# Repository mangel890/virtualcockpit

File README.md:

# virtualcockpit
Virtual Boeing 737 Cockpit

This is a project to build my own Boeing 737 cockpit
It is based on Arduino and Flight Simulator

This is on early stages now, many more changes are needed

Arduino/ contains a arduino .ino file for the MCP of the 737

CNC/ Sketch developed for my CNC that helps drilling the panels

PCB/ Different boards developed for extending input and output in Arduino Mega

Drawings/ Sketch developed for printing the MCP of the 737

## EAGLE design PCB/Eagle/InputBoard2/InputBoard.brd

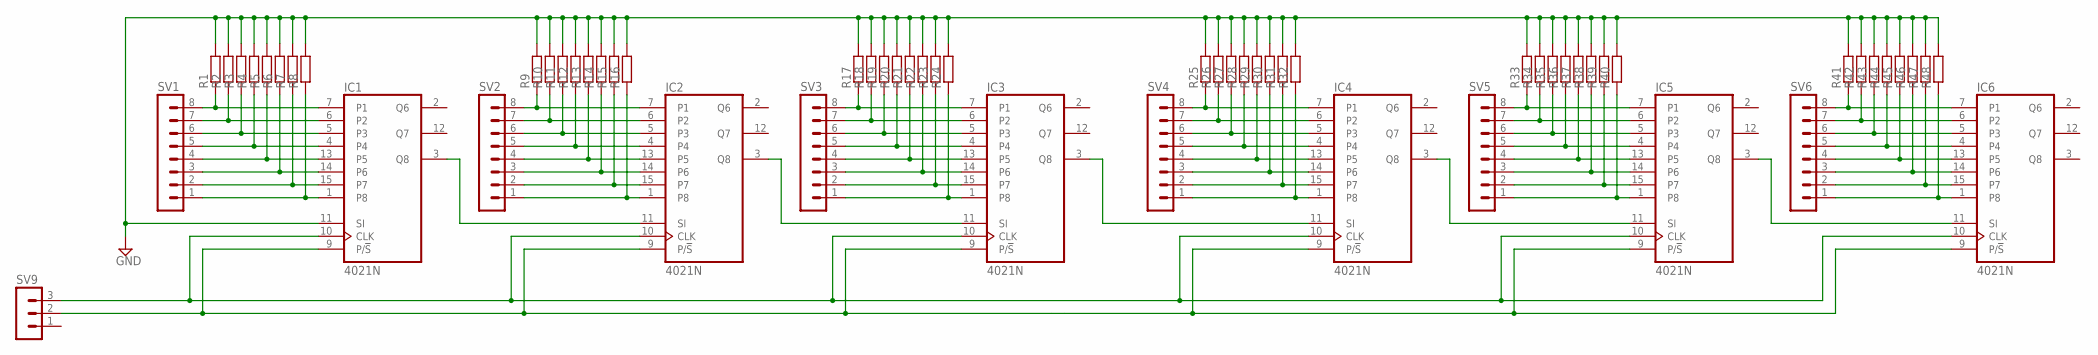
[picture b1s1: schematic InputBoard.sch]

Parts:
IC1, IC2, IC3, IC4, IC5, IC6: 4021N; DIL16
R1, R2, R3, R4, R5, R6, R7, R8, R9, R10, R11, R12, R13, R14, R15, R16, R17, R18, R19, R20, R21, R22, R23, R24, R25, R26, R27, R28, R29, R30, R31, R32, R33, R34, R35, R36, R37, R38, R39, R40, R41, R42, R43, R44, R45, R46, R47, R48: R-EU_0207/10; 0207/10
SV1, SV2, SV3, SV4, SV5, SV6: MA08-1
SV9: MA03-1

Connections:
GND: IC1.11 (SI), IC3.3 (Q8), IC4.11 (SI), R1.2, R2.2, R3.2, R4.2, R5.2, R6.2, R7.2, R8.2, R9.2, R10.2, R11.2, R12.2, R13.2, R14.2, R15.2, R16.2, R17.2, R18.2, R19.2, R20.2, R21.2, R22.2, R23.2, R24.2, R25.2, R26.2, R27.2, R28.2, R29.2, R30.2, R31.2, R32.2, R33.2, R34.2, R35.2, R36.2, R37.2, R38.2, R39.2, R40.2, R41.2, R42.2, R43.2, R44.2, R45.2, R46.2, R47.2, R48.2
unnamed: IC4.7 (P1), R25.1, SV4.8
unnamed: IC1.10 (CLK), IC2.10 (CLK), IC3.10 (CLK), IC4.10 (CLK), IC5.10 (CLK), IC6.10 (CLK), SV9.3
unnamed: IC1.3 (Q8), IC2.11 (SI)
unnamed: IC2.7 (P1), R9.1, SV2.8
unnamed: IC4.5 (P3), R27.1, SV4.6
unnamed: IC2.5 (P3), R11.1, SV2.6
unnamed: IC2.4, R12.1, SV2.5
unnamed: IC2.13 (P5), R13.1, SV2.4
unnamed: IC2.14 (P6), R14.1, SV2.3
unnamed: IC1.7 (P1), R1.1, SV1.8
unnamed: IC1.6 (P2), R2.1, SV1.7
unnamed: IC1.5 (P3), R3.1, SV1.6
unnamed: IC1.4, R4.1, SV1.5
unnamed: IC1.13 (P5), R5.1, SV1.4
unnamed: IC1.14 (P6), R6.1, SV1.3
unnamed: IC1.15 (P7), R7.1, SV1.2
unnamed: IC1.1 (P8), R8.1, SV1.1
unnamed: IC2.15 (P7), R15.1, SV2.2
unnamed: IC2.6 (P2), R10.1, SV2.7
unnamed: IC2.1 (P8), R16.1, SV2.1
unnamed: IC3.7 (P1), R17.1, SV3.8
unnamed: IC3.5 (P3), R19.1, SV3.6
unnamed: IC1.9 (P/!S), IC2.9 (P/!S), IC3.9 (P/!S), IC4.9 (P/!S), IC5.9 (P/!S), IC6.9 (P/!S), SV9.2
unnamed: IC3.4, R20.1, SV3.5
unnamed: IC3.13 (P5), R21.1, SV3.4
unnamed: IC3.14 (P6), R22.1, SV3.3
unnamed: IC3.15 (P7), R23.1, SV3.2
unnamed: IC3.6 (P2), R18.1, SV3.7
unnamed: IC3.1 (P8), R24.1, SV3.1
unnamed: IC4.4, R28.1, SV4.5
unnamed: IC2.3 (Q8), IC3.11 (SI)
unnamed: IC4.13 (P5), R29.1, SV4.4
unnamed: IC4.14 (P6), R30.1, SV4.3
unnamed: IC4.15 (P7), R31.1, SV4.2
unnamed: IC4.6 (P2), R26.1, SV4.7
unnamed: IC4.1 (P8), R32.1, SV4.1
unnamed: IC5.7 (P1), R33.1, SV5.8
unnamed: IC5.5 (P3), R35.1, SV5.6
unnamed: IC5.4, R36.1, SV5.5
unnamed: IC5.13 (P5), R37.1, SV5.4
unnamed: IC5.14 (P6), R38.1, SV5.3
unnamed: IC5.15 (P7), R39.1, SV5.2
unnamed: IC5.6 (P2), R34.1, SV5.7
unnamed: IC5.1 (P8), R40.1, SV5.1
unnamed: IC4.3 (Q8), IC5.11 (SI)
unnamed: IC6.7 (P1), R41.1, SV6.8
unnamed: IC6.5 (P3), R43.1, SV6.6
unnamed: IC6.4, R44.1, SV6.5
unnamed: IC6.13 (P5), R45.1, SV6.4
unnamed: IC6.14 (P6), R46.1, SV6.3
unnamed: IC6.15 (P7), R47.1, SV6.2
unnamed: IC6.6 (P2), R42.1, SV6.7
unnamed: IC6.1 (P8), R48.1, SV6.1
unnamed: IC5.3 (Q8), IC6.11 (SI)
VDD: IC1.16 (VDD), IC2.16 (VDD), IC3.16 (VDD), IC4.16 (VDD), IC5.16 (VDD), IC6.16 (VDD)
VSS: IC1.8 (VSS), IC2.8 (VSS), IC3.8 (VSS), IC4.8 (VSS), IC5.8 (VSS), IC6.8 (VSS)

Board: 2 copper layers, 61 parts (0 on the bottom side), 57 nets, no tracks yet.

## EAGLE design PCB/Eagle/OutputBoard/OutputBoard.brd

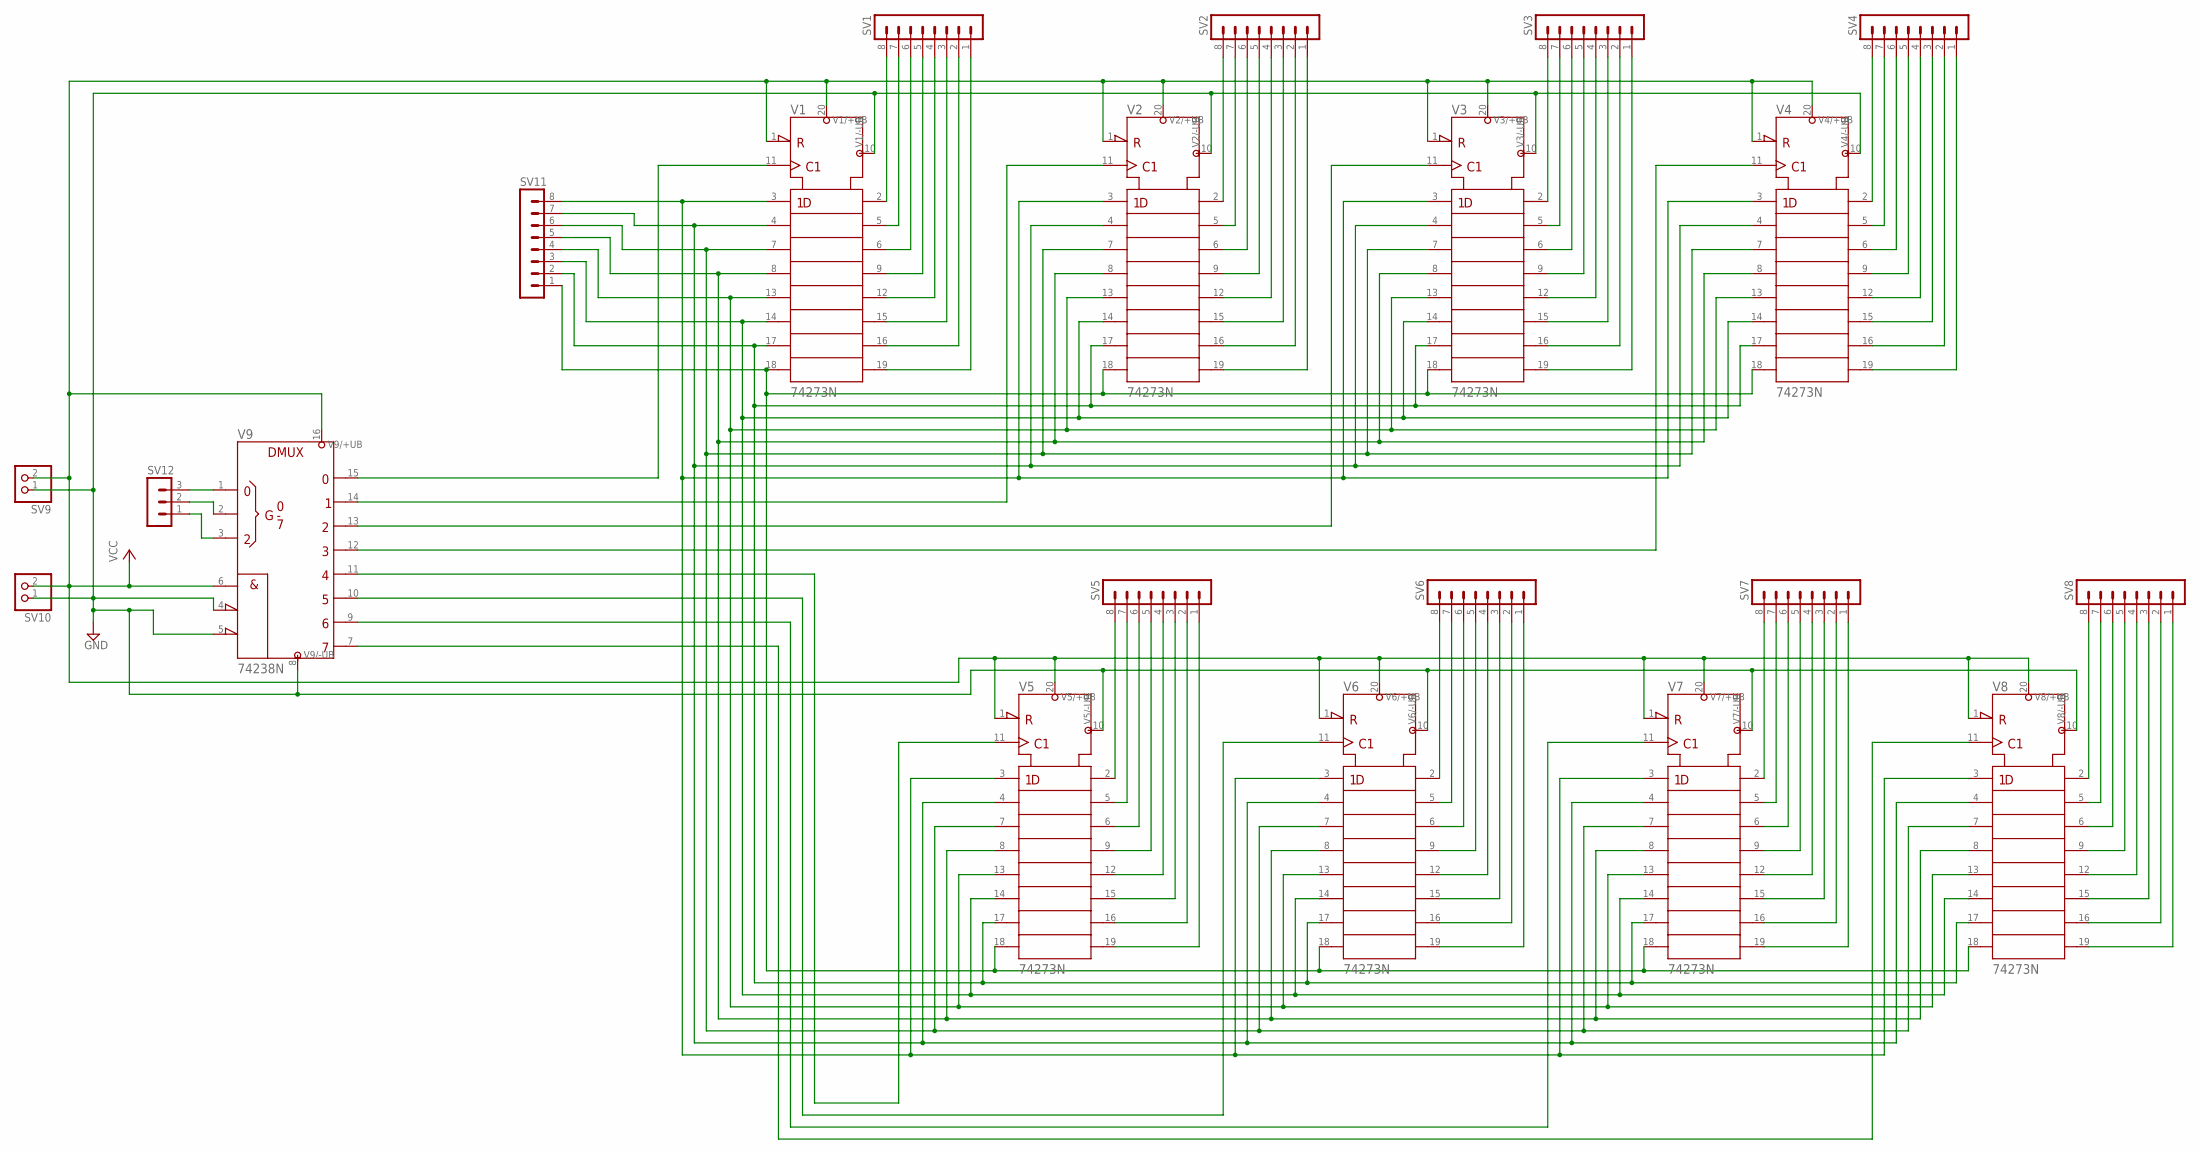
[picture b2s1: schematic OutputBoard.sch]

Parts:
SV1, SV2, SV3, SV4, SV5, SV6, SV7, SV8, SV11: MA08-1
SV9, SV10: PINHD-1X2; 1X02
SV12: MA03-1
V1, V2, V3, V4, V5, V6, V7, V8: 74273N; DIL20
V9: 74238N; DIL16

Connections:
BUS1: SV11.8, V1.3 (1D), V2.3 (1D), V3.3 (1D), V4.3 (1D), V5.3 (1D), V6.3 (1D), V7.3 (1D), V8.3 (1D)
DATA1: SV11.1, V1.18 (8D), V2.18 (8D), V3.18 (8D), V4.18 (8D), V5.18 (8D), V6.18 (8D), V7.18 (8D), V8.18 (8D)
DATA2: SV11.2, V1.17 (7D), V2.17 (7D), V3.17 (7D), V4.17 (7D), V5.17 (7D), V6.17 (7D), V7.17 (7D), V8.17 (7D)
DATA3: SV11.3, V1.14 (6D), V2.14 (6D), V3.14 (6D), V4.14 (6D), V5.14 (6D), V6.14 (6D), V7.14 (6D), V8.14 (6D)
DATA8: SV11.4, V1.13 (5D), V2.13 (5D), V3.13 (5D), V4.13 (5D), V5.13 (5D), V6.13 (5D), V7.13 (5D), V8.13 (5D)
GND: SV9.1, SV10.1, V1.10 (-UB), V2.10 (-UB), V3.10 (-UB), V4.10 (-UB), V5.10 (-UB), V6.10 (-UB), V7.10 (-UB), V8.10 (-UB), V9.4 (!G2A), V9.5 (!G2B), V9.8 (-UB)
unnamed: V3.11 (CLK), V9.13 (Y2)
unnamed: SV2.8, V2.2 (1Q)
unnamed: V1.11 (CLK), V9.15 (Y0)
unnamed: V2.11 (CLK), V9.14 (Y1)
unnamed: SV2.7, V2.5 (2Q)
unnamed: SV2.6, V2.6 (3Q)
unnamed: SV2.5, V2.9 (4Q)
unnamed: SV2.4, V2.12 (5Q)
unnamed: SV2.3, V2.15 (6Q)
unnamed: SV2.2, V2.16 (7Q)
unnamed: SV2.1, V2.19 (8Q)
unnamed: SV1.8, V1.2 (1Q)
unnamed: SV12.2, V9.2 (B)
unnamed: SV12.1, V9.3 (C)
unnamed: SV5.8, V5.2 (1Q)
unnamed: SV1.7, V1.5 (2Q)
unnamed: SV1.6, V1.6 (3Q)
unnamed: SV1.5, V1.9 (4Q)
unnamed: SV1.4, V1.12 (5Q)
unnamed: SV12.3, V9.1 (A)
unnamed: SV5.7, V5.5 (2Q)
unnamed: SV5.6, V5.6 (3Q)
unnamed: SV1.3, V1.15 (6Q)
unnamed: SV1.2, V1.16 (7Q)
unnamed: SV1.1, V1.19 (8Q)
unnamed: V4.11 (CLK), V9.12 (Y3)
unnamed: V5.11 (CLK), V9.11 (Y4)
unnamed: V6.11 (CLK), V9.10 (Y5)
unnamed: SV11.7, V1.4 (2D), V2.4 (2D), V3.4 (2D), V4.4 (2D), V5.4 (2D), V6.4 (2D), V7.4 (2D), V8.4 (2D)
unnamed: SV3.8, V3.2 (1Q)
unnamed: SV3.7, V3.5 (2Q)
unnamed: SV3.6, V3.6 (3Q)
unnamed: SV3.5, V3.9 (4Q)
unnamed: SV3.4, V3.12 (5Q)
unnamed: SV3.3, V3.15 (6Q)
unnamed: SV3.2, V3.16 (7Q)
unnamed: SV3.1, V3.19 (8Q)
unnamed: SV4.8, V4.2 (1Q)
unnamed: SV4.7, V4.5 (2Q)
unnamed: SV4.6, V4.6 (3Q)
unnamed: SV4.5, V4.9 (4Q)
unnamed: SV4.4, V4.12 (5Q)
unnamed: SV4.3, V4.15 (6Q)
unnamed: SV4.2, V4.16 (7Q)
unnamed: SV4.1, V4.19 (8Q)
unnamed: SV11.6, V1.7 (3D), V2.7 (3D), V3.7 (3D), V4.7 (3D), V5.7 (3D), V6.7 (3D), V7.7 (3D), V8.7 (3D)
unnamed: SV11.5, V1.8 (4D), V2.8 (4D), V3.8 (4D), V4.8 (4D), V5.8 (4D), V6.8 (4D), V7.8 (4D), V8.8 (4D)
unnamed: SV6.8, V6.2 (1Q)
unnamed: SV6.7, V6.5 (2Q)
unnamed: SV6.6, V6.6 (3Q)
unnamed: SV6.5, V6.9 (4Q)
unnamed: SV6.4, V6.12 (5Q)
unnamed: SV6.3, V6.15 (6Q)
unnamed: SV6.2, V6.16 (7Q)
unnamed: SV6.1, V6.19 (8Q)
unnamed: SV7.8, V7.2 (1Q)
unnamed: SV7.7, V7.5 (2Q)
unnamed: SV7.6, V7.6 (3Q)
unnamed: SV7.5, V7.9 (4Q)
unnamed: SV7.4, V7.12 (5Q)
unnamed: SV7.3, V7.15 (6Q)
unnamed: SV7.2, V7.16 (7Q)
unnamed: SV7.1, V7.19 (8Q)
unnamed: V7.11 (CLK), V9.9 (Y6)
unnamed: SV8.8, V8.2 (1Q)
unnamed: SV8.7, V8.5 (2Q)
unnamed: SV8.6, V8.6 (3Q)
unnamed: SV8.5, V8.9 (4Q)
unnamed: SV8.4, V8.12 (5Q)
unnamed: SV8.3, V8.15 (6Q)
unnamed: SV8.2, V8.16 (7Q)
unnamed: SV8.1, V8.19 (8Q)
unnamed: SV5.5, V5.9 (4Q)
unnamed: SV5.4, V5.12 (5Q)
unnamed: SV5.3, V5.15 (6Q)
unnamed: SV5.2, V5.16 (7Q)
unnamed: SV5.1, V5.19 (8Q)
unnamed: V8.11 (CLK), V9.7 (Y7)
VCC: SV9.2, SV10.2, V1.1 (!CLR), V1.20 (+UB), V2.1 (!CLR), V2.20 (+UB), V3.1 (!CLR), V3.20 (+UB), V4.1 (!CLR), V4.20 (+UB), V5.1 (!CLR), V5.20 (+UB), V6.1 (!CLR), V6.20 (+UB), V7.1 (!CLR), V7.20 (+UB), V8.1 (!CLR), V8.20 (+UB), V9.6 (G1), V9.16 (+UB)

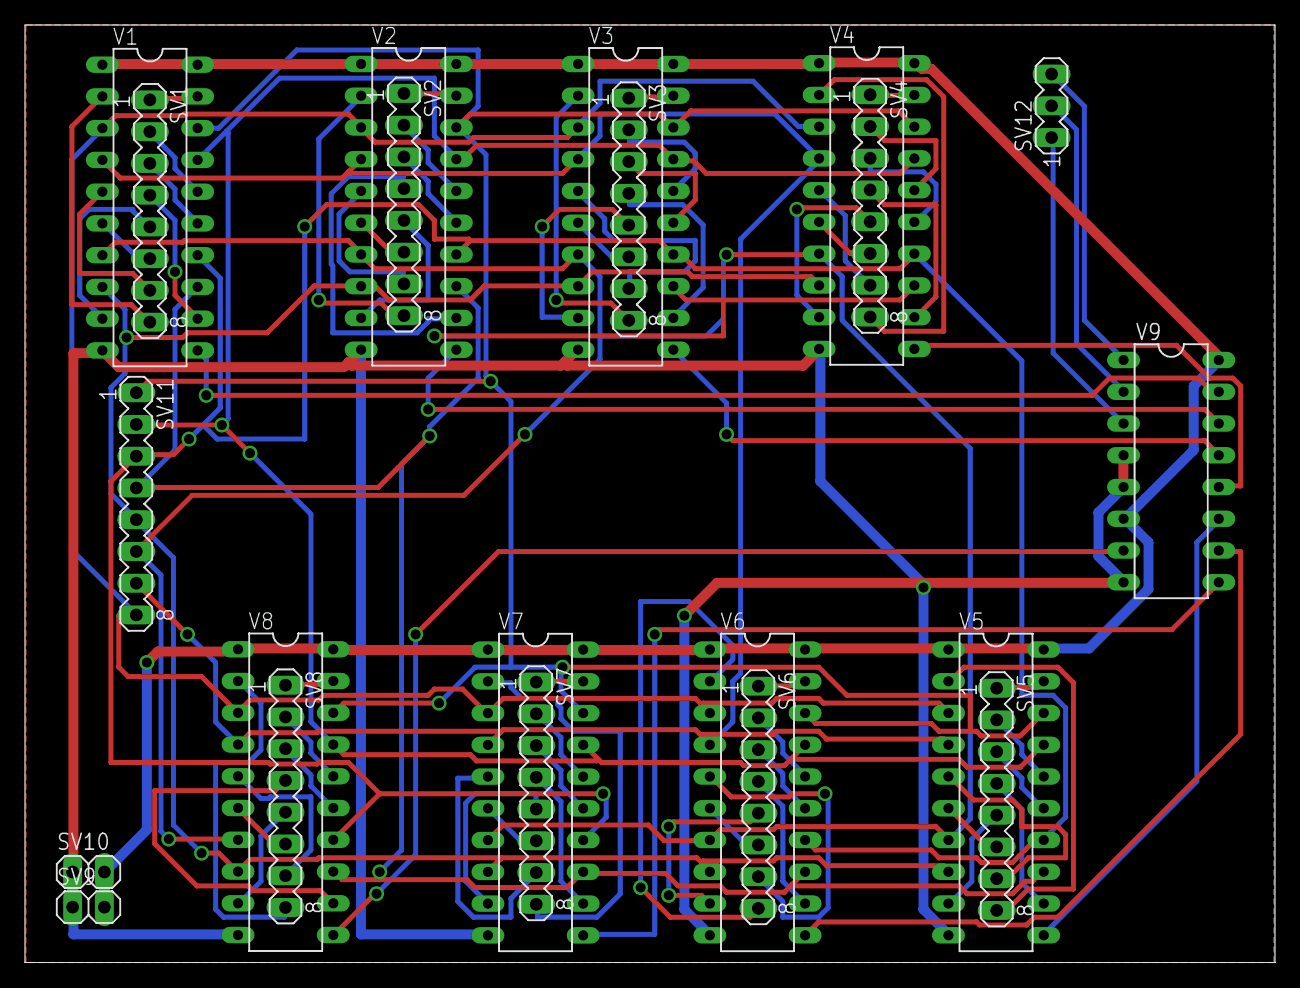
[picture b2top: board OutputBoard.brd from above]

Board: 2 copper layers, 100.0 x 75.0 mm, 21 parts (0 on the bottom side), 85 nets.

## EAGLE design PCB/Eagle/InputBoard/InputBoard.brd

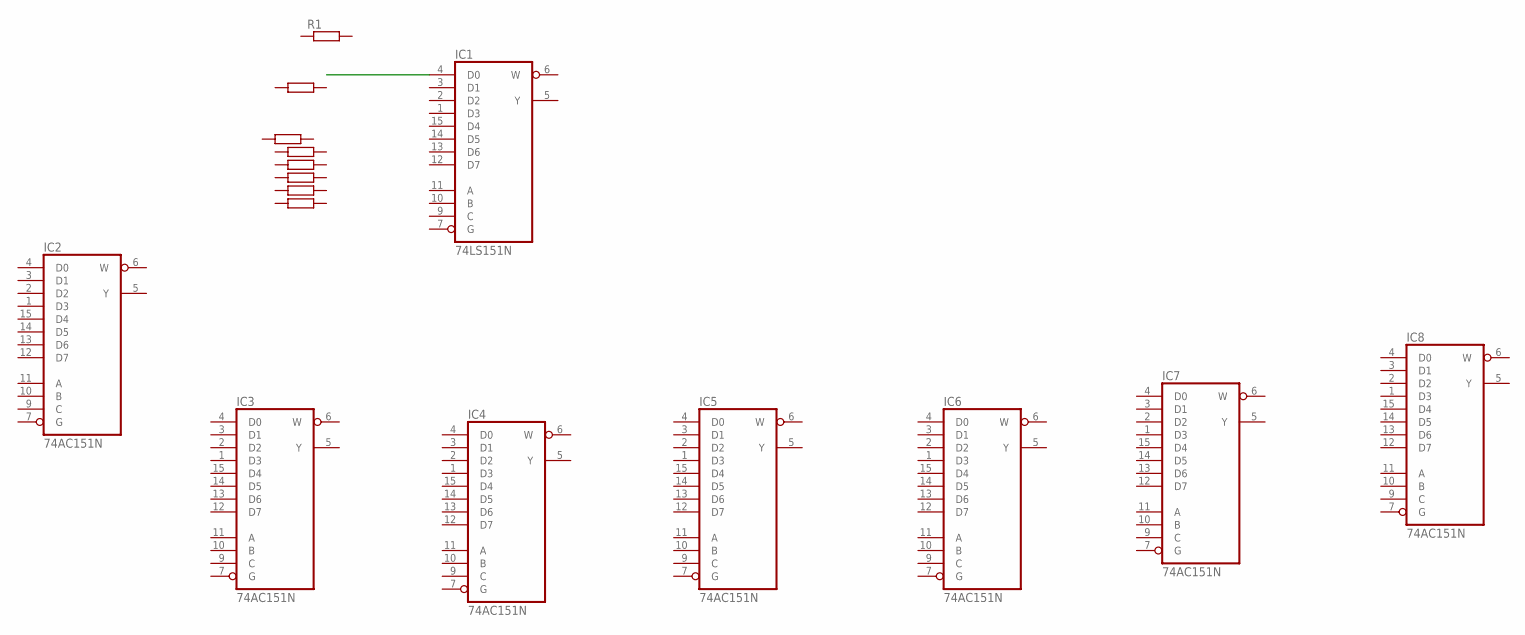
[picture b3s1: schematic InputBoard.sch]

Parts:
IC1: 74LS151N; DIL16
IC2, IC3, IC4, IC5, IC6, IC7, IC8: 74AC151N; DIL16
R1: R-EU_0207/10; 0207/10

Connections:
GND: IC1.8 (GND), IC2.8 (GND), IC3.8 (GND), IC4.8 (GND), IC5.8 (GND), IC6.8 (GND), IC7.8 (GND), IC8.8 (GND)
VCC: IC1.16 (VCC), IC2.16 (VCC), IC3.16 (VCC), IC4.16 (VCC), IC5.16 (VCC), IC6.16 (VCC), IC7.16 (VCC), IC8.16 (VCC)

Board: 2 copper layers, 9 parts (0 on the bottom side), 2 nets, no tracks yet.

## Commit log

2014-08-30 First commit. I need git. This commit would need to undo some changes on the serial library that I'm doing for testing it at high speed.
2014-08-30 Removed sdf file which is binary and autogenerated
2014-08-30 Added gitIgnore and solution file for Visual C++ project
2014-08-30 Back to normal. Now it works fine. Serial 8B Odd Par and 2StopBits
    Still looses messages
2014-09-04 Arduino buffer for serial port.
    Send commands from Processing to Arduino at maximum speed
2014-09-04 Buffer Problems fixed Now every data from processing to Arduino gets correctly
2014-09-09 Displays show less intensity for '1' and '7'
2014-09-09 AT Arm led works by using FSUIPC
2014-09-09 MCP panel blueprint
2014-09-10 Fixed problem with paths in panels
2014-09-10 Adapted Displays with 5 digits (altitude and vspeed) and some other fixes
2014-09-14 PCB Boards started in Eagle and Fritzing
2014-09-14 Couple of libraries added. This is not good practice but we need them
2014-09-14 Added git ignore for pcb files
2014-09-18 Blank display for IAS and updates in PCB boards
2014-09-20 Added guide for FSUIPC offsets in PMDG
2014-09-20 Added support for iasBlank and Underspeed/Overspeed flashes
2014-09-20 Mach view in IAS display and serial port initialized before PMDG data is sent
2014-09-28 Second autopilot and FD working. Disengage bar working as Toggle
2014-09-28 New InputBoard and some modifications to OutputBoard
2014-10-05 Two more digits for altitude and vertical speed. Null display when zeros on the leftside.
2014-10-09 PCB Modified with proper flip flop 74 273 and ground fill
2015-03-15 Correct initialization of PMDGIf to fetch data from FSX
2015-03-15 Eagle PDF files removed
    Conflicts:
    PCB/Eagle/OutputBoard/OutputBoardBottom.pdf
    PCB/Eagle/OutputBoard/OutputBoardTop.pdf
2015-03-15 Possible routing for two sides and full board
    Conflicts:
    PCB/Eagle/OutputBoard/OutputBoard.brd
    PCB/Eagle/OutputBoard/OutputBoard.sch
    PCB/Eagle/OutputBoard/eagle.epf
2015-03-15 PCB files ready for print, with polygons but no VCC or GND. Good routing
    Conflicts:
    PCB/Eagle/OutputBoard/OutputBoard.brd
    PCB/Eagle/OutputBoard/OutputBoard.sch
    PCB/Eagle/OutputBoard/eagle.epf
2015-03-15 CNC started
2015-03-15 Changes to CNC model
2015-03-15 Modifs to CNC file
2015-03-15 More Modifs
2015-03-15 More updates to CNC (Minor: couplers)
2015-03-15 VC project in PCClient adapted to VC2013
2015-03-15 GitIgnore files changed
2015-03-15 CNC: Better hierarchy, more annotations and more standard measurements
2015-03-15 Updates in CNC: Ball Bearings
2015-03-15 Some minor adjustments on anotations
2015-03-15 PDF Files added for printing data of CNC
2015-03-15 Change in view
2015-03-15 New output board based on serial controllers
2015-03-15 Fixes due to missing blob in repository
    THe eagle files for Output Board since 2014-10-16 22:07:17 may be wrong in history
2015-03-19 Change to English in 'drawings' and better readme file
2015-03-21 Commenting the Arduino file
2015-03-29 Some more input & output boards
2015-05-15 Input Board in DesignSpark ready for milling
2015-07-11 Minor changes
2015-07-12 Gcode for Input board from DesignSpark
2016-01-31 FSUIPC removed as it is no longer needed
    Adapted to new version of VS Studio
2016-01-31 Useful URLs added
2016-03-13 Finally a flow to convert to gcode from Inkscape
2016-10-02 Handling couple of messages in simconnect loop
2016-10-02 Negative prints in PCB for Input Board added
2016-10-19 Thicker tracks, pads and vias in InputBoard
2016-10-29 Guide for getting good PCBs with dry film
2016-11-01 added reference to SDK file
2016-11-15 Images added for wiki
    Unfortunately there is no other way to submit images and guarantee that
    they will be available forever. Github recommends to add images to own
    repos.
